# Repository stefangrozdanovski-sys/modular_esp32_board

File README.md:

# Modular ESP32 board (ESP32 Modular Base v2.0)

An open-hardware ESP32 carrier for Home Assistant / ESPHome. It has 8 JST XH 4-pin ports:

- **P1–P6**: general ports, each with a digital pin **A** and an input/analog pin **B**
- **UART**: 5 V serial port for meters and RS485 modules
- **I2C**: sensor bus with pull-ups fitted

There is also a switched output (**OUT**) for 12–24 V loads. Every general port has the same set of empty resistor footprints; you fit a few to match the job:

- **Generic jobs:** relays, buttons and dry contacts, temperature probes, 0–3.3 V analog signals, pulse and flow meters, energy meters, RS485 Modbus devices, I2C sensors and displays, 12–24 V loads (SSR, LED strip, fan, buzzer)
- **Popular parts:** 1–8 channel relay modules, DS18B20, NTC 10 k thermistors, YF-S201 / YF-B flow sensors, PZEM-004T v3, MAX485 modules, BME280, SHT3x / SHT4x, BH1750, ADS1115, SSD1306 OLED, capacitive soil moisture sensors

> **Status: v2.0 PCBs received from Seeed Studio (2026-11-05), not yet built or tested.**
> The picture below is rendered from the Gerbers, not a photo. Real photos and a test report will be added after bring-up.

## Features

- Ai-Thinker ESP-32S / ESP32-WROOM-32 module, USB (CH340C) with auto-reset, BOOT/RESET buttons, status LED
- 75 × 65 mm, 2 layers, hand-solderable (0805, 1206, SOT-23/223, SOIC-16, THT)
- Also suitable for machine assembly: standard SMD packages, assembly files for JLCPCB / PCBWay in `production/pcba/`
- 6 general ports P1–P6 (G, VP, A, B), UART port (5 V, RX divider for 5 V devices), I2C port (pull-ups fitted)
- OUT: low-side MOSFET switch with flyback diode, about 2 A / 24 V, PWM-capable
- Per port: VP jumper (3.3 V / 5 V), 0.5 A PTC, series resistors, empty footprints for pull-ups, pull-downs, divider and filter
- **Low voltage only.** No mains on the PCB. Mains devices (e.g. PZEM-004T, relay boards) stay in their own enclosure section behind a divider. Flash and probe the board with mains disconnected.

## Pin map

| Port | A (pin 3) | B (pin 4) | Notes |
|---|---|---|---|
| P1 | GPIO25 | GPIO36 | B input-only, ADC1. No pulse counting on GPIO36 |
| P2 | GPIO26 | GPIO39 | B input-only, ADC1. No pulse counting on GPIO39 |
| P3 | GPIO27 | GPIO34 | B input-only, ADC1 |
| P4 | GPIO13 | GPIO35 | B input-only, ADC1 |
| P5 | GPIO4 | GPIO32 | B bidirectional, ADC1 |
| P6 | GPIO18 | GPIO33 | B bidirectional, ADC1 |
| UART | TX GPIO17 | RX GPIO16 | VP = 5 V, RX through 10 k / 22 k divider |
| I2C | SDA GPIO21 | SCL GPIO22 | 4.7 k pull-ups fitted |
| OUT | GPIO23 → AO3400A | | XH 3P: G, V+, OUT |
| Fixed | GPIO0 BOOT, GPIO1/3 USB serial, GPIO2 status LED | | |

Connector pins: 1 GND, 2 VP, 3 A, 4 B (JST XH 2.54 mm, pin 1 = square pad).

## Port recipes

Fit the parts for the job, then use the matching ESPHome component.

| Job | Pin | VP | Fit | ESPHome |
|---|---|---|---|---|
| Relay module, low trigger | A | 3V3 | defaults | `switch: gpio`, `inverted: true` |
| Relay module, high trigger | A | 3V3 | + RAD 10 k | `switch: gpio` |
| DS18B20 | A | 3V3 | + RAU 4.7 k | `one_wire` + `dallas_temp` |
| Button / dry contact | A | – | internal pull-up (or RAU 10 k) | `binary_sensor: gpio` |
| NTC 10 k B3950 | B | – | + RBU 10 k 1 %, CB 100 nF | `adc` → `resistance` → `ntc` |
| 0–3.3 V analog | B | as needed | + CB 100 nF | `adc` |
| 5 V pulse (flow sensor) | B on P3–P6 | 5V | RB → 10 k, + RBD 22 k, CB 1 nF | `pulse_counter` |
| Open-collector pulse | A | 5V | + RAU 10 k | `pulse_counter` |
| PZEM-004T | UART | 5V | defaults | `uart` + `modbus` + `pzemac` |
| RS485 Modbus | UART + P5/P6 B (DE/RE) | 5V | remove R706 for a 3.3 V module | `modbus` with `flow_control_pin` |
| I2C sensors | I2C | 3V3 | defaults | `i2c` + sensor |
| SSR / LED strip / fan / buzzer | OUT | load supply | defaults | `output: ledc` or `gpio` |

Part names per port (n = port number, 7 = UART, 8 = I2C): Rn01 RA series, Rn02 RAU, Rn03 RAD, Rn04 RB series, Rn05 RBU, Rn06 RBD, Cn01 CB. Full details: the "Port options" sheet in [the BOM workbook](hardware/bom/esp32-modular-v2.0-BOM.xlsx) and page 13+ of the assembly guide.

## Build one

**Bare PCB:** upload [`hardware/fabrication/esp32-modular_gerbers.zip`](hardware/fabrication/esp32-modular_gerbers.zip) to JLCPCB, PCBWay or Seeed Fusion: 2 layers, 75 × 65 mm, 1.6 mm, 1 oz, HASL lead-free (ENIG is nicer for the module's castellated pads). All rules are within the standard tier.

**Hand assembly:**
- [Assembly guide (A4 PDF, 17 pages)](hardware/docs/assembly_guide.pdf): one page per soldering step, inspection and test pages
- [Interactive BOM](hardware/docs/ibom_assembly.html): download it and open it in a browser, then click a part to see where it goes
- [BOM workbook](hardware/bom/esp32-modular-v2.0-BOM.xlsx) and [BOM app](hardware/bom/bom-app.html) (offline shopping list: stock, shops, number of boards)
- [Schematic (PDF)](hardware/docs/schematic.pdf)

**Assembled by the fab (PCBA):** JLCPCB and PCBWay BOM and position files are in [`production/pcba/`](production/pcba/README.md). They cover the 54 SMD parts; you hand-solder the 14 THT parts (XH sockets, buttons, electrolytics) or pay JLCPCB for THT assembly. The fab build uses an ESP32-WROOM-32E-N4 instead of the Ai-Thinker ESP-32S. All LCSC numbers were checked on JLCPCB (2026-11-05). **Before ordering:** confirm part rotations in JLCPCB's placement preview (see that README).

## Firmware

ESPHome packages in [`firmware/`](firmware/README.md): one package per port job (relay, dry contact, DS18B20, NTC, analog, pulse flow, PZEM-004T, RS485 Modbus, I2C + BME280, OUT PWM / switch), a common `base.yaml` with the board pins as substitutions, and three examples (`test-board`, `energy-relay`, `greenhouse`).

Pick the job, fit the parts from the recipe above, then include the package with the port pin:

```yaml
packages:
  base: !include ../base.yaml
  pump_p1: !include
    file: ../packages/relay.yaml
    vars: {id: pump_p1, name: Pump, pin: "${p1_a}"}
```

Every example passes `esphome config` on ESPHome 2026.10.2 (ESP-IDF framework). Not yet run on a built board. New board: flash `firmware/examples/test-board.yaml` first (assembly guide page 13).

## Setup notes

- [ ] **PCBA:** confirm every part's rotation and pin 1 in JLCPCB's placement preview before any assembled order (see [`production/pcba/README.md`](production/pcba/README.md)).
- [ ] **Flow sensors:** set `pulses_per_litre` for each flow sensor model used. One board set can use different models, so set it per sensor (typical values in [`firmware/README.md`](firmware/README.md#flow-sensor-factors)).
- [ ] **Device sets:** the examples are starting points. Write one device config per board set (which devices on which ports), named after the board (e.g. `b1-boiler.yaml`).

## Repository

| Folder | Contents |
|---|---|
| `firmware/` | ESPHome packages and example configs. See [firmware/README.md](firmware/README.md) |
| `hardware/` | KiCad 7 project, custom footprint library, generator scripts (`tools/`), BOM (`bom/`), docs and Gerbers. See [hardware/README.md](hardware/README.md) |
| `production/pcba/` | JLCPCB / PCBWay BOM and position files, generated by `hardware/tools/pcba.py` |
| `LICENSES/` | Licence texts |

The KiCad files are generated by Python scripts (`hardware/tools/`): `parts.py` and `design.py` are the source of truth. Rebuild steps and the toolchain (KiCad 7, Freerouting 1.9.0, InteractiveHtmlBom, …) are in [hardware/README.md](hardware/README.md). KiCad 8/9 open the files and upgrade them on save.

## Known caveats

- Hardware not yet built or tested. Faults found during bring-up will be logged in [CHANGELOG.md](CHANGELOG.md) and the issues.
- Electrical check done with a netlist pin-type script (`erc_lite.py`), not a full KiCad GUI ERC. Expected finding: CH340C V3 and AMS1117 output both on +3V3 (CH340C 3.3 V mode).
- Six reference designators are hidden on the silkscreen for lack of room. The iBOM and assembly guide show all of them.
- Iron temperatures and test values in the assembly guide are general guidance, not measurements from a built board.

## Licence

| What | Licence |
|---|---|
| Hardware design (KiCad files, footprints, Gerbers) | [CERN-OHL-S-2.0](LICENSES/CERN-OHL-S-2.0.txt) |
| Scripts and firmware | [MIT](LICENSES/MIT.txt) |
| Documentation and images | [CC BY-SA 4.0](LICENSES/CC-BY-SA-4.0.txt) |

© 2026 stefangrozdanovski-sys. Freerouting (used to route the board, downloaded by `hardware/tools/get_freerouting.sh`) is GPL-3.0 and not included.

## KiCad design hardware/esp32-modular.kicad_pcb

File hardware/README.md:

# ESP32 Modular Base v2.0: hardware

75 × 65 mm, 2 layers, 1.6 mm FR-4. Hand-solderable (0805, 1206, SOT-23/223, SOIC-16, THT).
Low-voltage board only: USB 5 V in, no mains on the PCB.

## Connectors

| Edge | Connector | Pins (pin 1 = square pad) |
|---|---|---|
| Top-right | J1 USB in (XH 4P) | 5V, D−, D+, G (from the bare USB-C breakout, A-to-C cable) |
| Bottom | P1–P4 (J101–J401, XH 4P) | G, VP, A, B |
| Left | P5, P6 (J501, J601, XH 4P) | G, VP, A, B |
| Right | UART (J701), I2C (J801), XH 4P | G, VP, TX, RX / G, VP, SDA, SCL |
| Right | OUT (J901, XH 3P) | G, V+, OUT |
| Under module | EXP (J902, 1×5 2.54 mm, not fitted) | 3V3, IO19, IO14, IO5, G |
| Top-left | RESET, BOOT buttons | |

## Pin map

| Port | A (pin 3) | B (pin 4) | Notes |
|---|---|---|---|
| P1 | IO25 | IO36 | B input-only, ADC1. No pulse counting on IO36 |
| P2 | IO26 | IO39 | B input-only, ADC1. No pulse counting on IO39 |
| P3 | IO27 | IO34 | B input-only, ADC1 |
| P4 | IO13 | IO35 | B input-only, ADC1 |
| P5 | IO4 | IO32 | B bidirectional, ADC1 |
| P6 | IO18 | IO33 | B bidirectional, ADC1 |
| UART | TX IO17 | RX IO16 | RX through 10k/22k divider (5 V devices) |
| I2C | SDA IO21 | SCL IO22 | 4.7 k pull-ups fitted |
| OUT | IO23 → AO3400A | | low-side, SS34 flyback to V+, about 2 A / 24 V |
| Fixed | IO0 BOOT, IO1/IO3 CH340C, IO2 status LED | | |

The port map is also printed on the back of the board.

## Port options (same in every port, n = port number, 7 = UART, 8 = I2C)

| Ref | Position | Default |
|---|---|---|
| JPn01 | VP jumper: pad next to the connector = 3V3, far pad = 5V | 3V3 (UART: 5V), bridged by a trace |
| Fn01 | 0.5 A PTC on VP | fitted |
| Rn01 | A series | 330 R |
| Rn02 / Rn03 | A pull-up to 3V3 / pull-down to GND | empty |
| Rn04 | B series | 1 k |
| Rn05 | B pull-up to 3V3 (connector side) | empty |
| Rn06 / Cn01 | B to GND (GPIO side): divider bottom / filter | empty |

To change a VP jumper: cut the thin trace between the bridged pads, then bridge the other side with solder.
Recipes for each job (relay, NTC, DS18B20, flow sensor, PZEM, I2C) are on the "Port options" sheet of `bom/esp32-modular-v2.0-BOM.xlsx`.

## Buying the parts

Open `bom/bom-app.html` in your browser (works offline). Enter what you have in stock, set the number of boards, choose the shop per part, then open the Shopping list tab and print it on A4. Everything is saved in that browser; use Export backup to keep a copy. Rebuild it with `python3 bom/build_bom_app.py bom/bom-app.html` after the BOM changes.

## Ordering

Upload `fabrication/esp32-modular_gerbers.zip` to PCBWay or JLCPCB: 2 layers, 75 × 65 mm, 1.6 mm, 1 oz, HASL lead-free (ENIG is nicer for the castellated module).
Rules used: 0.2 mm clearance, 0.3 mm signal / 0.4 mm power tracks, 0.7/0.35 mm vias (tented), 0.5 mm copper to edge. All within the standard tier.

## Assembly order

Print `docs/assembly_guide.pdf` (17 A4 pages): one page per soldering step with the parts highlighted on a board drawing, tick boxes for boards B1–B5, inspection, test pages with measurement columns, port options, jumper how-to, a board record and a parts index.

Open `docs/ibom_assembly.html` in a browser: click a BOM line and its parts light up on the board (pin 1 marked). Tick Sourced / Placed as you go; the ticks are remembered in that browser. Empty option footprints are not listed.

1. Fine pitch first, board flat: U3 CH340C, U4 USBLC6, Q1, Q2, Q901, U2 AMS1117.
2. 0805 / 1206 parts: the core first, then each port's fitted parts (Rn01 330 R, Rn04 1 k, Fn01 PTC, plus R706 22 k, R704 10 k, R802/R805 4.7 k).
   Leave the option footprints empty until you know what goes on that port.
3. D1 SMAJ5.0A and D901 SS34 (band toward +5V / V+), F1, LEDs (cathode toward GND).
4. U1 ESP-32S: tin pad 1, align, tack pads 1 and 38, check, then drag-solder. Optionally solder the centre GND pad through the hole from the back.
5. THT: SW1/SW2, C1/C4 (mind the +), XH sockets.

## Bring-up

1. Unpowered: +5V–GND and +3V3–GND are not shorted.
2. Power from USB: +5V ≈ 4.9–5.1 V, +3V3 = 3.25–3.35 V, red LED on.
3. Plug into a PC: the CH340 appears as a serial port. Flash ESPHome; auto-reset handles boot mode (or hold BOOT, tap RESET).

## Verification done

- Netlist vs `tools/design.py`: 73 nets, 119 parts, 0 differences. Pin-type electrical check: only the documented CH340C 3.3 V mode finding.
- KiCad 7 DRC: 0 violations, 0 unconnected items, 0 footprint errors.
- PCB vs schematic: all 325 pads carry the schematic's net.
- Gerbers re-read with gerbv; `docs/board_top.png` / `board_bottom.png` are rendered from the Gerbers.

## Rebuilding (tools/)

`parts.py` (values, footprints, fit) and `design.py` (nets) are the source of truth; `layout.py` holds the board geometry and placement.

```
python3 tools/gen_sch.py esp32-modular.kicad_sch
kicad-cli sch export netlist -o net.net esp32-modular.kicad_sch
python3 tools/check_net.py net.net && python3 tools/erc_lite.py net.net
python3 tools/build_pcb.py net.net placed.kicad_pcb
python3 tools/silk_fix.py placed.kicad_pcb silk.kicad_pcb --keepout
bash tools/get_freerouting.sh                                    # once: downloads Freerouting 1.9.0 (GPL-3.0)
python3 tools/route.py silk.kicad_pcb routed.kicad_pcb 60        # Freerouting 1.9.0, optimizer off
python3 tools/finish.py routed.kicad_pcb fin.kicad_pcb drc.txt --stitch
python3 tools/polish.py fin.kicad_pcb esp32-modular.kicad_pcb net.net
python3 tools/verify_pcb.py esp32-modular.kicad_pcb net.net drc.txt
bash tools/export.sh .
python3 tools/board_geom.py esp32-modular.kicad_pcb docs/assembly/geom.json
python3 tools/assembly_book.py docs/assembly/geom.json docs/assembly/assembly_guide.html
python3 tools/print_pdf.py docs/assembly/assembly_guide.html docs/assembly_guide.pdf     # A4 assembly guide
bash tools/make_ibom.sh . net.net                                # docs/ibom_assembly.html
python3 tools/gerber_render.py fabrication/gerbers docs/board_top.png docs/board_bottom.png
python3 bom/build_bom.py bom/esp32-modular-v2.0-BOM.xlsx
```

In a bare Python session set `KICAD7_FOOTPRINT_DIR=/usr/share/kicad/footprints`. Remove the `silk: no vias` rule areas after routing (done before saving the project board).

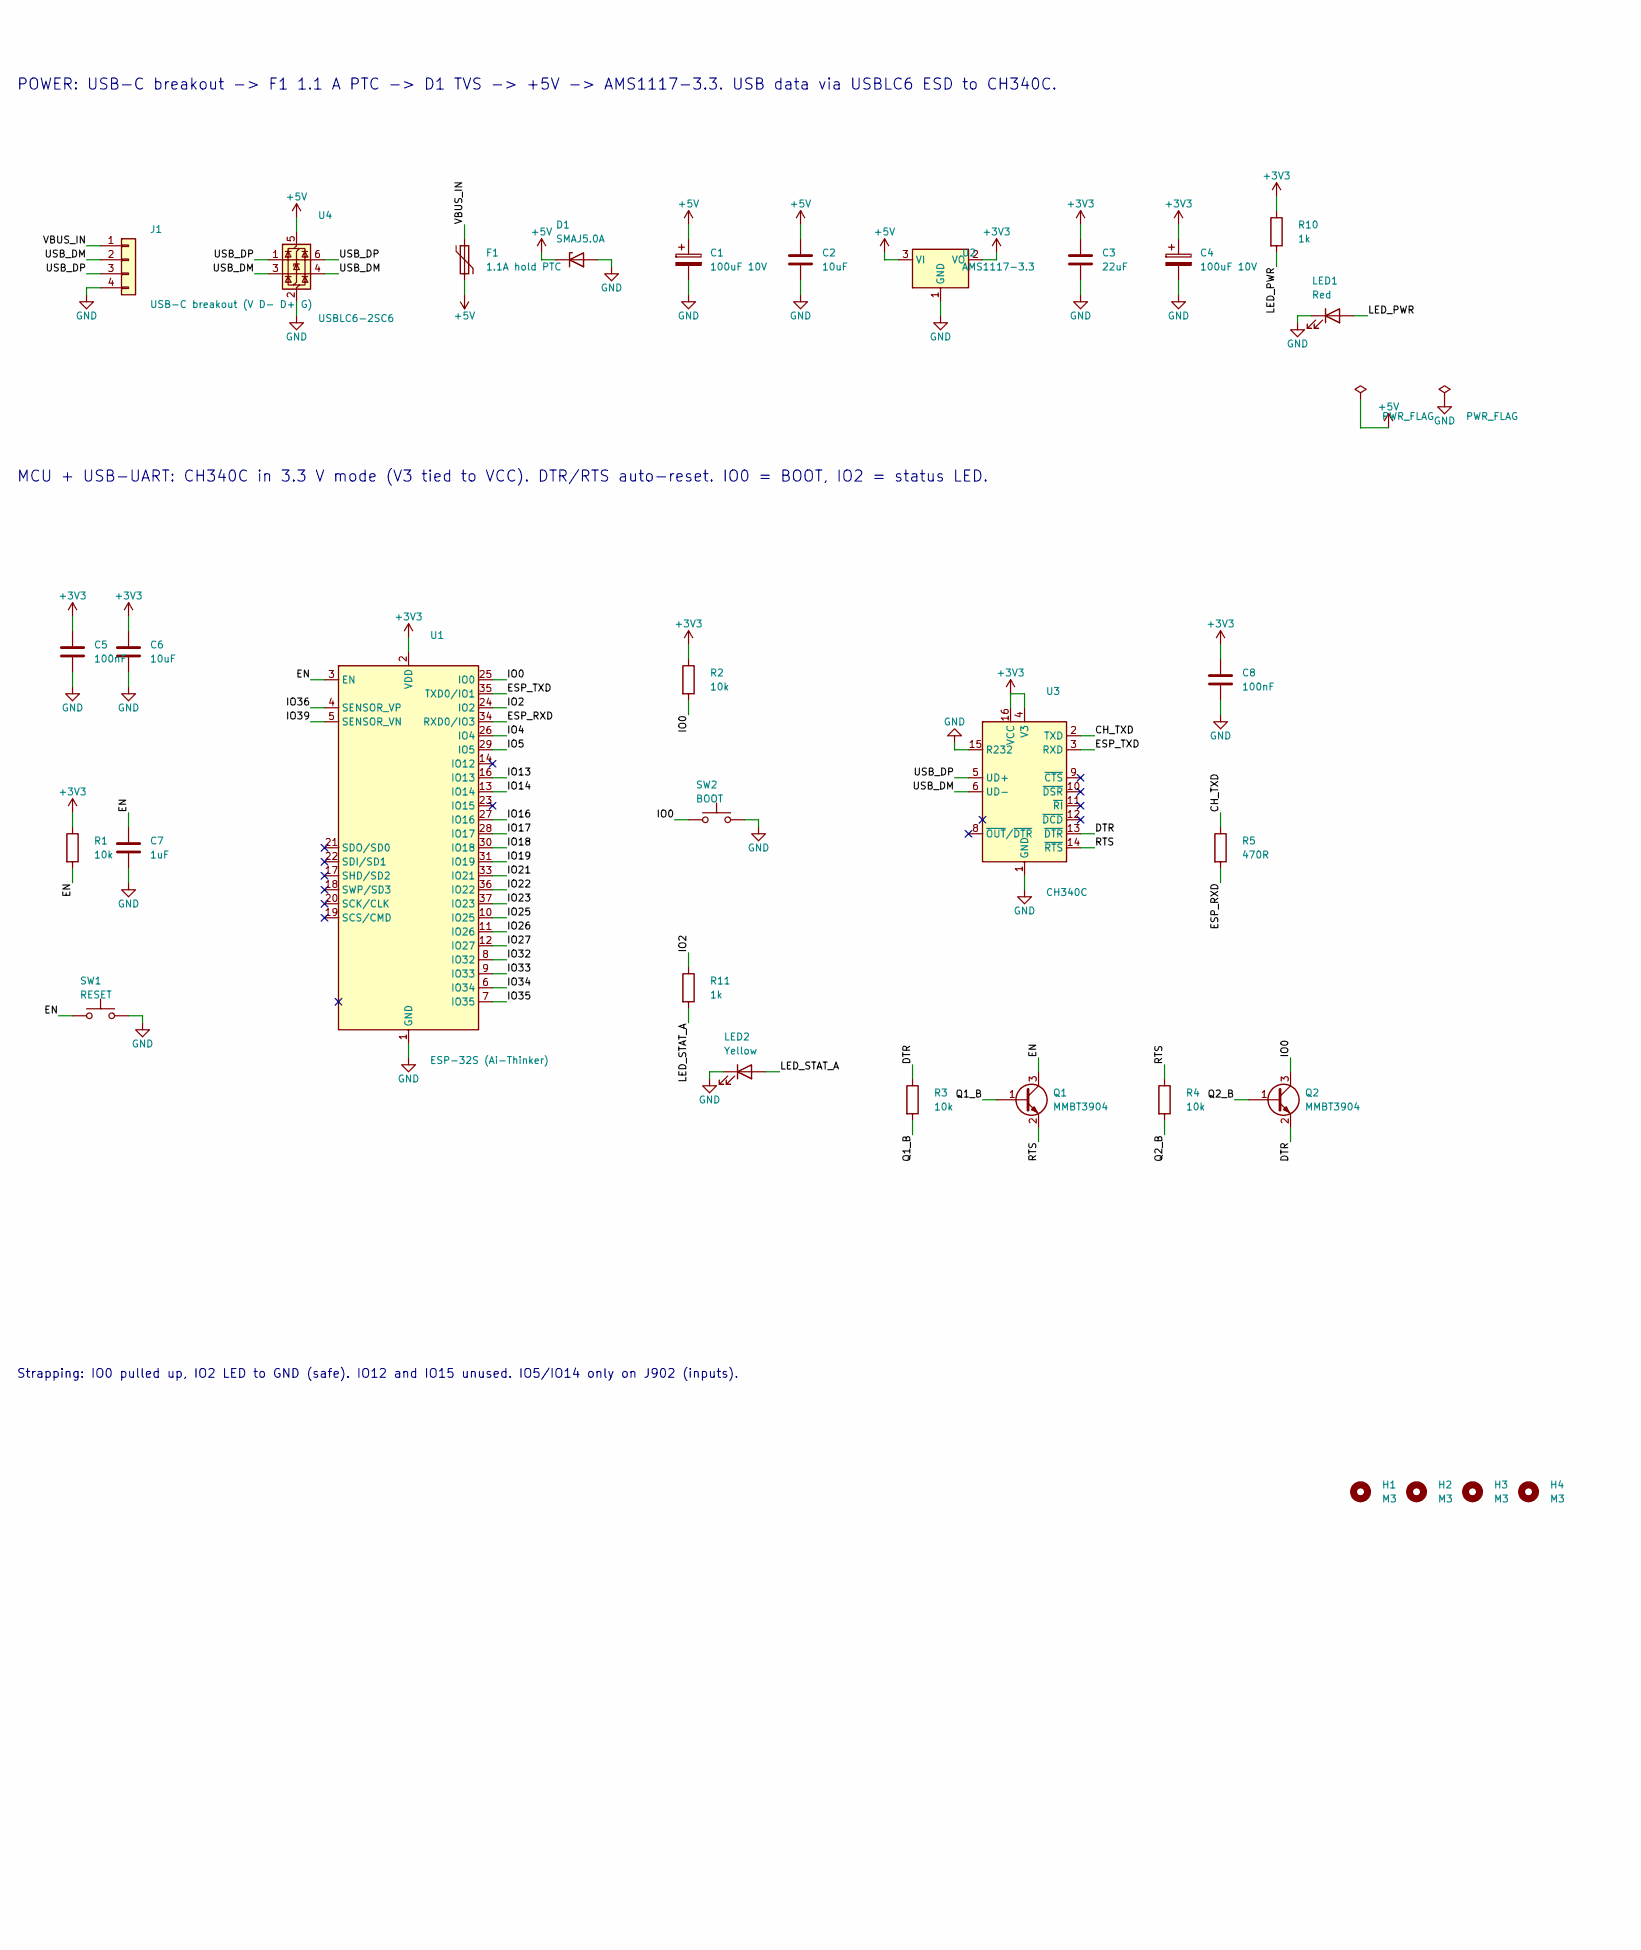
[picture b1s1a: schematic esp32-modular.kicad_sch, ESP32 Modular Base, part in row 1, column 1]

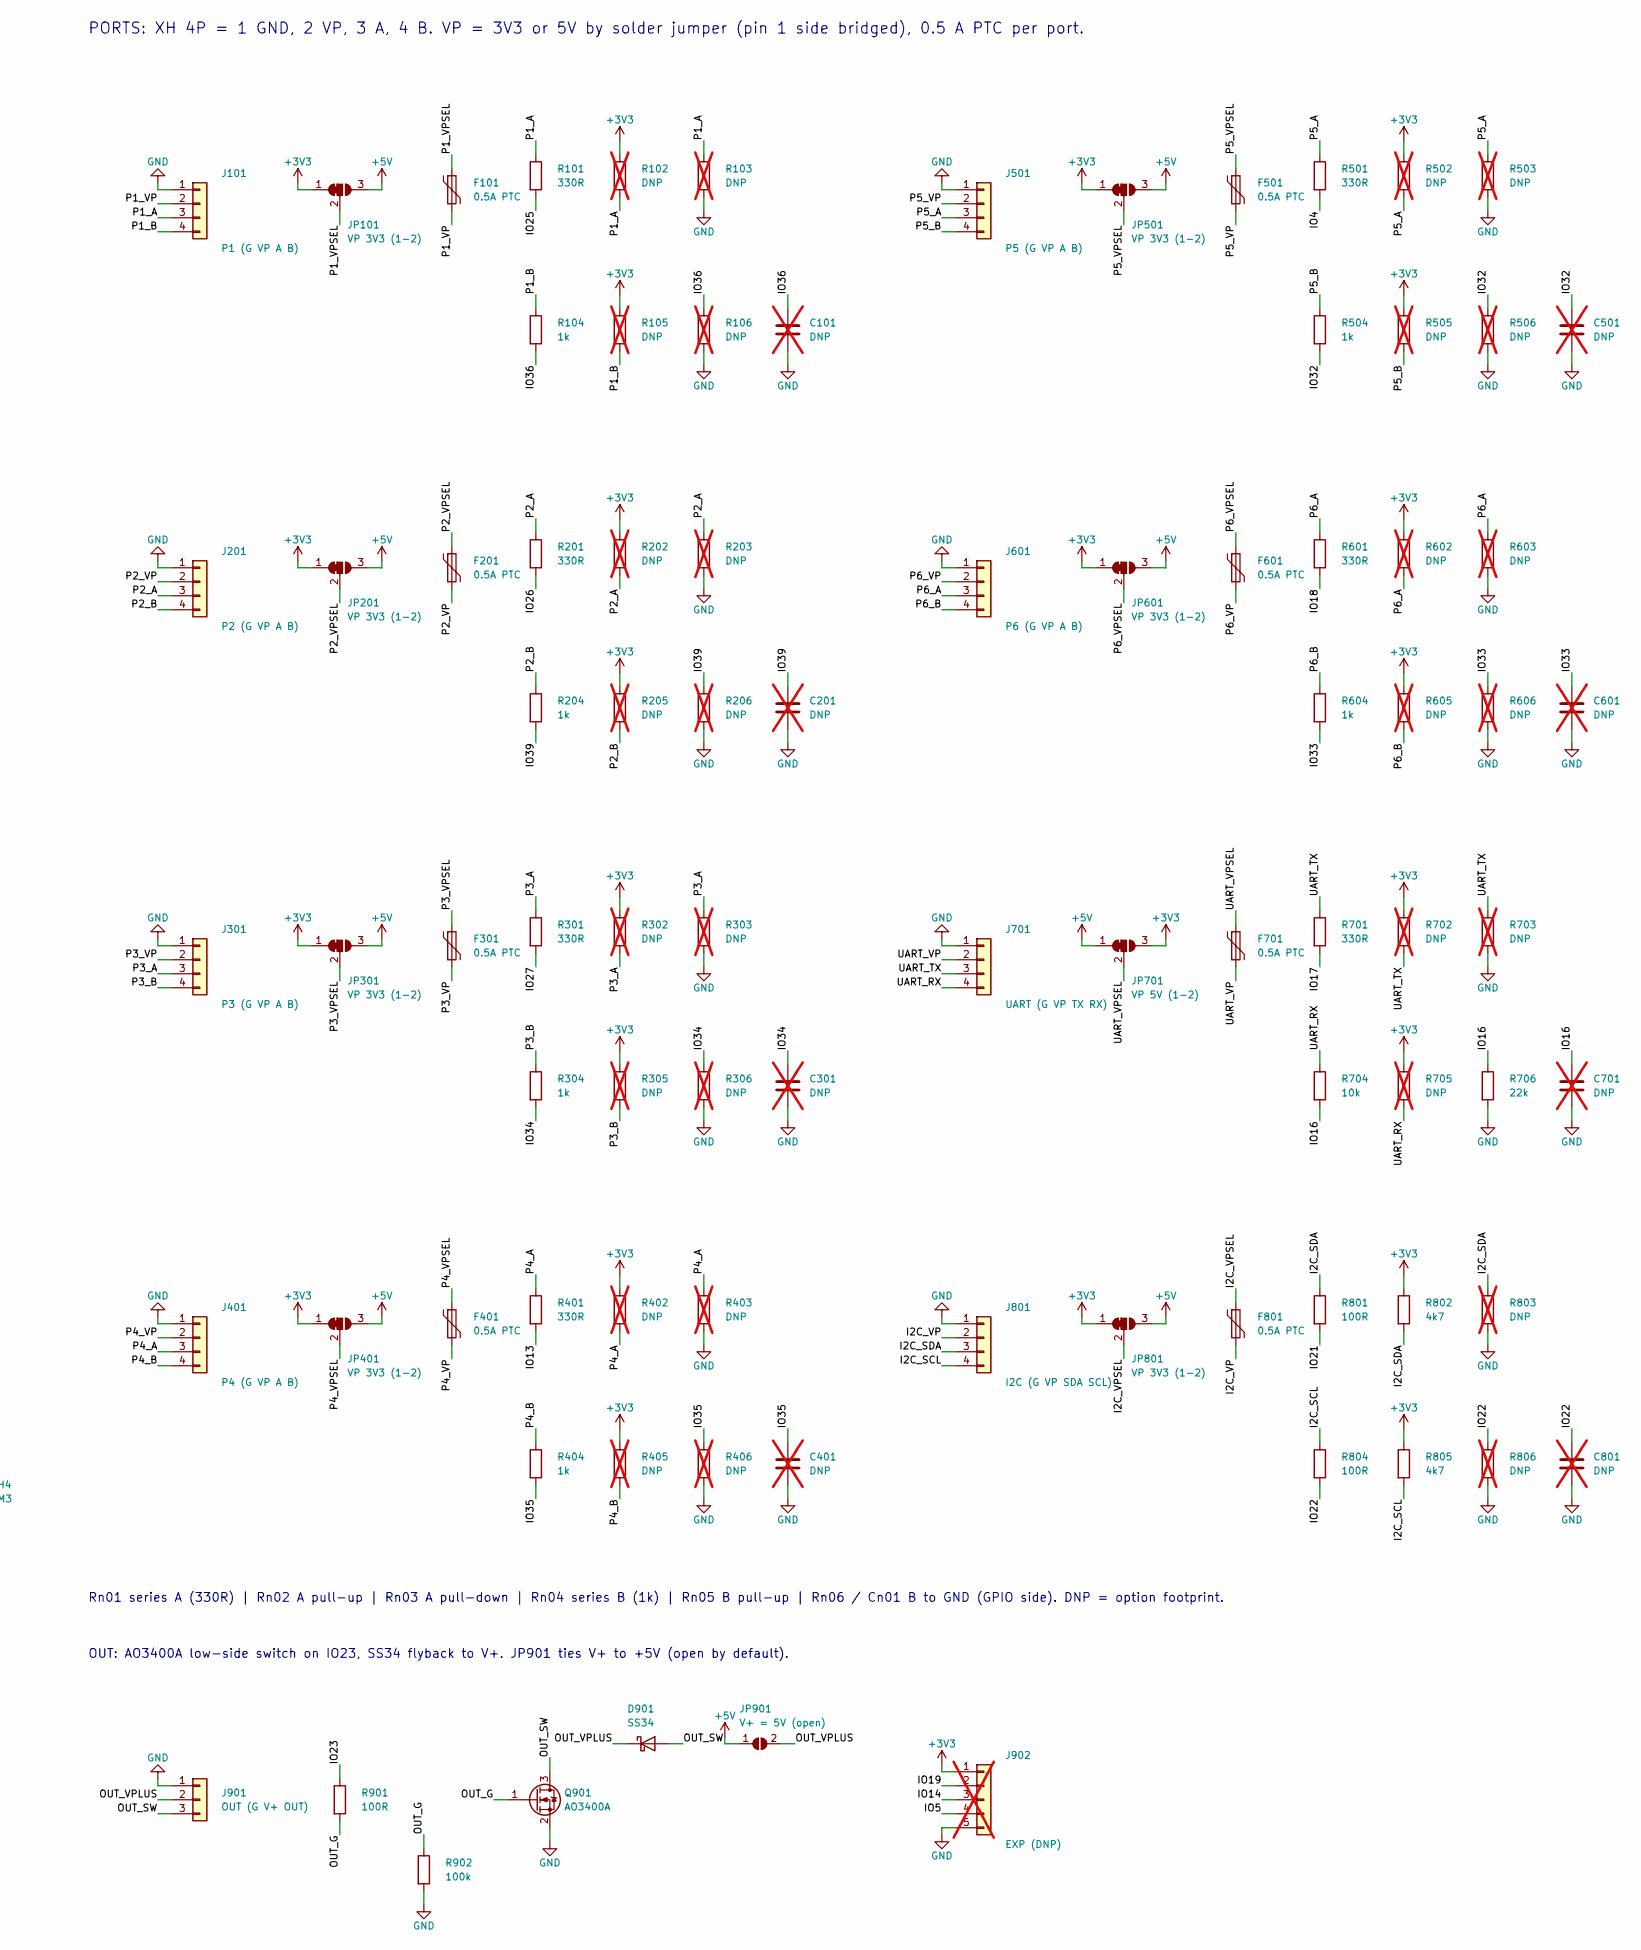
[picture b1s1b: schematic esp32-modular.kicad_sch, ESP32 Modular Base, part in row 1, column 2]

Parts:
C1, C4: 100uF 10V; CP_Radial_D6.3mm_P2.50mm
C2, C6: 10uF; C_0805_2012Metric_Pad1.18x1.45mm_HandSolder
C3: 22uF; C_0805_2012Metric_Pad1.18x1.45mm_HandSolder
C5, C8: 100nF; C_0805_2012Metric_Pad1.18x1.45mm_HandSolder
C7: 1uF; C_0805_2012Metric_Pad1.18x1.45mm_HandSolder
C101, C201, C301, C401, C501, C601, C701, C801: DNP; C_0805_2012Metric_Pad1.18x1.45mm_HandSolder; not fitted
D1: SMAJ5.0A; D_SMA_Handsoldering
D901: SS34; D_SMA_Handsoldering
F1: 1.1A hold PTC; Fuse_1812_4532Metric_Pad1.30x3.40mm_HandSolder
F101, F201, F301, F401, F501, F601, F701, F801: 0.5A PTC; Fuse_1206_3216Metric_Pad1.42x1.75mm_HandSolder
H1, H2, H3, H4: M3; MountingHole_3.2mm_M3
J1: USB-C breakout (V D- D+ G); JST_XH_B4B-XH-A_1x04_P2.50mm_Vertical
J101: P1 (G VP A B); JST_XH_B4B-XH-A_1x04_P2.50mm_Vertical
J201: P2 (G VP A B); JST_XH_B4B-XH-A_1x04_P2.50mm_Vertical
J301: P3 (G VP A B); JST_XH_B4B-XH-A_1x04_P2.50mm_Vertical
J401: P4 (G VP A B); JST_XH_B4B-XH-A_1x04_P2.50mm_Vertical
J501: P5 (G VP A B); JST_XH_B4B-XH-A_1x04_P2.50mm_Vertical
J601: P6 (G VP A B); JST_XH_B4B-XH-A_1x04_P2.50mm_Vertical
J701: UART (G VP TX RX); JST_XH_B4B-XH-A_1x04_P2.50mm_Vertical
J801: I2C (G VP SDA SCL); JST_XH_B4B-XH-A_1x04_P2.50mm_Vertical
J901: OUT (G V+ OUT); JST_XH_B3B-XH-A_1x03_P2.50mm_Vertical
J902: EXP (DNP); PinHeader_1x05_P2.54mm_Vertical; not fitted
JP101, JP201, JP301, JP401, JP501, JP601, JP801: VP 3V3 (1-2); SolderJumper-3_P1.3mm_Bridged12_RoundedPad1.0x1.5mm
JP701: VP 5V (1-2); SolderJumper-3_P1.3mm_Bridged12_RoundedPad1.0x1.5mm
JP901: V+ = 5V (open); SolderJumper-2_P1.3mm_Open_RoundedPad1.0x1.5mm
LED1: Red; LED_0805_2012Metric_Pad1.15x1.40mm_HandSolder
LED2: Yellow; LED_0805_2012Metric_Pad1.15x1.40mm_HandSolder
Q1, Q2: MMBT3904; SOT-23
Q901: AO3400A; SOT-23
R1, R2, R3, R4, R704: 10k; R_0805_2012Metric_Pad1.20x1.40mm_HandSolder
R5: 470R; R_0805_2012Metric_Pad1.20x1.40mm_HandSolder
R10, R11, R104, R204, R304, R404, R504, R604: 1k; R_0805_2012Metric_Pad1.20x1.40mm_HandSolder
R101, R201, R301, R401, R501, R601, R701: 330R; R_0805_2012Metric_Pad1.20x1.40mm_HandSolder
R102, R103, R105, R106, R202, R203, R205, R206, R302, R303, R305, R306, R402, R403, R405, R406, R502, R503, R505, R506, R602, R603, R605, R606, R702, R703, R705, R803, R806: DNP; R_0805_2012Metric_Pad1.20x1.40mm_HandSolder; not fitted
R706: 22k; R_0805_2012Metric_Pad1.20x1.40mm_HandSolder
R801, R804, R901: 100R; R_0805_2012Metric_Pad1.20x1.40mm_HandSolder
R802, R805: 4k7; R_0805_2012Metric_Pad1.20x1.40mm_HandSolder
R902: 100k; R_0805_2012Metric_Pad1.20x1.40mm_HandSolder
SW1: RESET; SW_PUSH_6mm
SW2: BOOT; SW_PUSH_6mm
U1: ESP-32S (Ai-Thinker); ESP32-WROOM-32_HandSolder
U2: AMS1117-3.3; SOT-223-3_TabPin2
U3: CH340C; SOIC-16_3.9x9.9mm_P1.27mm
U4: USBLC6-2SC6; SOT-23-6

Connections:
+3V3: C3.1, C4.1, C5.1, C6.1, C8.1, J902.1, JP101.1 (A), JP201.1 (A), JP301.1 (A), JP401.1 (A), JP501.1 (A), JP601.1 (A), JP701.3 (B), JP801.1 (A), R1.1, R2.1, R10.1, R102.1, R105.1, R202.1, R205.1, R302.1, R305.1, R402.1, R405.1, R502.1, R505.1, R602.1, R605.1, R702.1, R705.1, R802.1, R805.1, U1.2 (VDD), U2.2 (VO), U3.4 (V3), U3.16 (VCC)
+5V: C1.1, C2.1, D1.1 (K), F1.2, JP101.3 (B), JP201.3 (B), JP301.3 (B), JP401.3 (B), JP501.3 (B), JP601.3 (B), JP701.1 (A), JP801.3 (B), JP901.1 (A), U2.3 (VI), U4.5 (VBUS)
/CH_TXD: R5.1, U3.2 (TXD)
/DTR: Q2.2 (E), R3.1, U3.13 (~DTR)
/EN: C7.1, Q1.3 (C), R1.2, SW1.1, U1.3 (EN)
/ESP_RXD: R5.2, U1.34 (RXD0/IO3)
/ESP_TXD: U1.35 (TXD0/IO1), U3.3 (RXD)
/I2C_SCL: J801.4, R804.1, R805.2
/I2C_SDA: J801.3, R801.1, R802.2, R803.1
/I2C_VP: F801.2, J801.2
/I2C_VPSEL: F801.1, JP801.2 (C)
/IO0: Q2.3 (C), R2.2, SW2.1, U1.25 (IO0)
/IO2: R11.1, U1.24 (IO2)
/IO4: R501.2, U1.26 (IO4)
/IO5: J902.4, U1.29 (IO5)
/IO13: R401.2, U1.16 (IO13)
/IO14: J902.3, U1.13 (IO14)
/IO16: C701.1, R704.2, R706.1, U1.27 (IO16)
/IO17: R701.2, U1.28 (IO17)
/IO18: R601.2, U1.30 (IO18)
/IO19: J902.2, U1.31 (IO19)
/IO21: R801.2, U1.33 (IO21)
/IO22: C801.1, R804.2, R806.1, U1.36 (IO22)
/IO23: R901.1, U1.37 (IO23)
/IO25: R101.2, U1.10 (IO25)
/IO26: R201.2, U1.11 (IO26)
/IO27: R301.2, U1.12 (IO27)
/IO32: C501.1, R504.2, R506.1, U1.8 (IO32)
/IO33: C601.1, R604.2, R606.1, U1.9 (IO33)
/IO34: C301.1, R304.2, R306.1, U1.6 (IO34)
/IO35: C401.1, R404.2, R406.1, U1.7 (IO35)
/IO36: C101.1, R104.2, R106.1, U1.4 (SENSOR_VP)
/IO39: C201.1, R204.2, R206.1, U1.5 (SENSOR_VN)
/LED_PWR: LED1.2 (A), R10.2
/LED_STAT_A: LED2.2 (A), R11.2
/OUT_G: Q901.1 (G), R901.2, R902.1
/OUT_SW: D901.2 (A), J901.3, Q901.3 (D)
/OUT_VPLUS: D901.1 (K), J901.2, JP901.2 (B)
/P1_A: J101.3, R101.1, R102.2, R103.1
/P1_B: J101.4, R104.1, R105.2
/P1_VP: F101.2, J101.2
/P1_VPSEL: F101.1, JP101.2 (C)
/P2_A: J201.3, R201.1, R202.2, R203.1
/P2_B: J201.4, R204.1, R205.2
/P2_VP: F201.2, J201.2
/P2_VPSEL: F201.1, JP201.2 (C)
/P3_A: J301.3, R301.1, R302.2, R303.1
/P3_B: J301.4, R304.1, R305.2
/P3_VP: F301.2, J301.2
/P3_VPSEL: F301.1, JP301.2 (C)
/P4_A: J401.3, R401.1, R402.2, R403.1
/P4_B: J401.4, R404.1, R405.2
/P4_VP: F401.2, J401.2
/P4_VPSEL: F401.1, JP401.2 (C)
/P5_A: J501.3, R501.1, R502.2, R503.1
/P5_B: J501.4, R504.1, R505.2
/P5_VP: F501.2, J501.2
/P5_VPSEL: F501.1, JP501.2 (C)
/P6_A: J601.3, R601.1, R602.2, R603.1
/P6_B: J601.4, R604.1, R605.2
/P6_VP: F601.2, J601.2
/P6_VPSEL: F601.1, JP601.2 (C)
/Q1_B: Q1.1 (B), R3.2
/Q2_B: Q2.1 (B), R4.2
/RTS: Q1.2 (E), R4.1, U3.14 (~RTS)
/UART_RX: J701.4, R704.1, R705.2
/UART_TX: J701.3, R701.1, R702.2, R703.1
/UART_VP: F701.2, J701.2
/UART_VPSEL: F701.1, JP701.2 (C)
/USB_DM: J1.2, U3.6 (UD-), U4.3 (I/O2), U4.4 (I/O2)
/USB_DP: J1.3, U3.5 (UD+), U4.1 (I/O1), U4.6 (I/O1)
/VBUS_IN: F1.1, J1.1
GND: C1.2, C2.2, C3.2, C4.2, C5.2, C6.2, C7.2, C8.2, C101.2, C201.2, C301.2, C401.2, C501.2, C601.2, C701.2, C801.2, D1.2 (A), J1.4, J101.1, J201.1, J301.1, J401.1, J501.1, J601.1, J701.1, J801.1, J901.1, J902.5, LED1.1 (K), LED2.1 (K), Q901.2 (S), R103.2, R106.2, R203.2, R206.2, R303.2, R306.2, R403.2, R406.2, R503.2, R506.2, R603.2, R606.2, R703.2, R706.2, R803.2, R806.2, R902.2, SW1.2, SW2.2, U1.1 (GND), U1.15 (GND), U1.38 (GND), U1.39 (GND), U2.1 (GND), U3.1 (GND), U3.15 (R232), U4.2 (GND)

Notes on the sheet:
POWER: USB-C breakout -> F1 1.1 A PTC -> D1 TVS -> +5V -> AMS1117-3.3. USB data via USBLC6 ESD to CH340C.
MCU + USB-UART: CH340C in 3.3 V mode (V3 tied to VCC). DTR/RTS auto-reset. IO0 = BOOT, IO2 = status LED.
Strapping: IO0 pulled up, IO2 LED to GND (safe). IO12 and IO15 unused. IO5/IO14 only on J902 (inputs).
PORTS: XH 4P = 1 GND, 2 VP, 3 A, 4 B. VP = 3V3 or 5V by solder jumper (pin 1 side bridged), 0.5 A PTC per port.
Rn01 series A (330R) | Rn02 A pull-up | Rn03 A pull-down | Rn04 series B (1k) | Rn05 B pull-up | Rn06 / Cn01 B to GND (GPIO side). DNP = option footprint.
OUT: AO3400A low-side switch on IO23, SS34 flyback to V+. JP901 ties V+ to +5V (open by default).

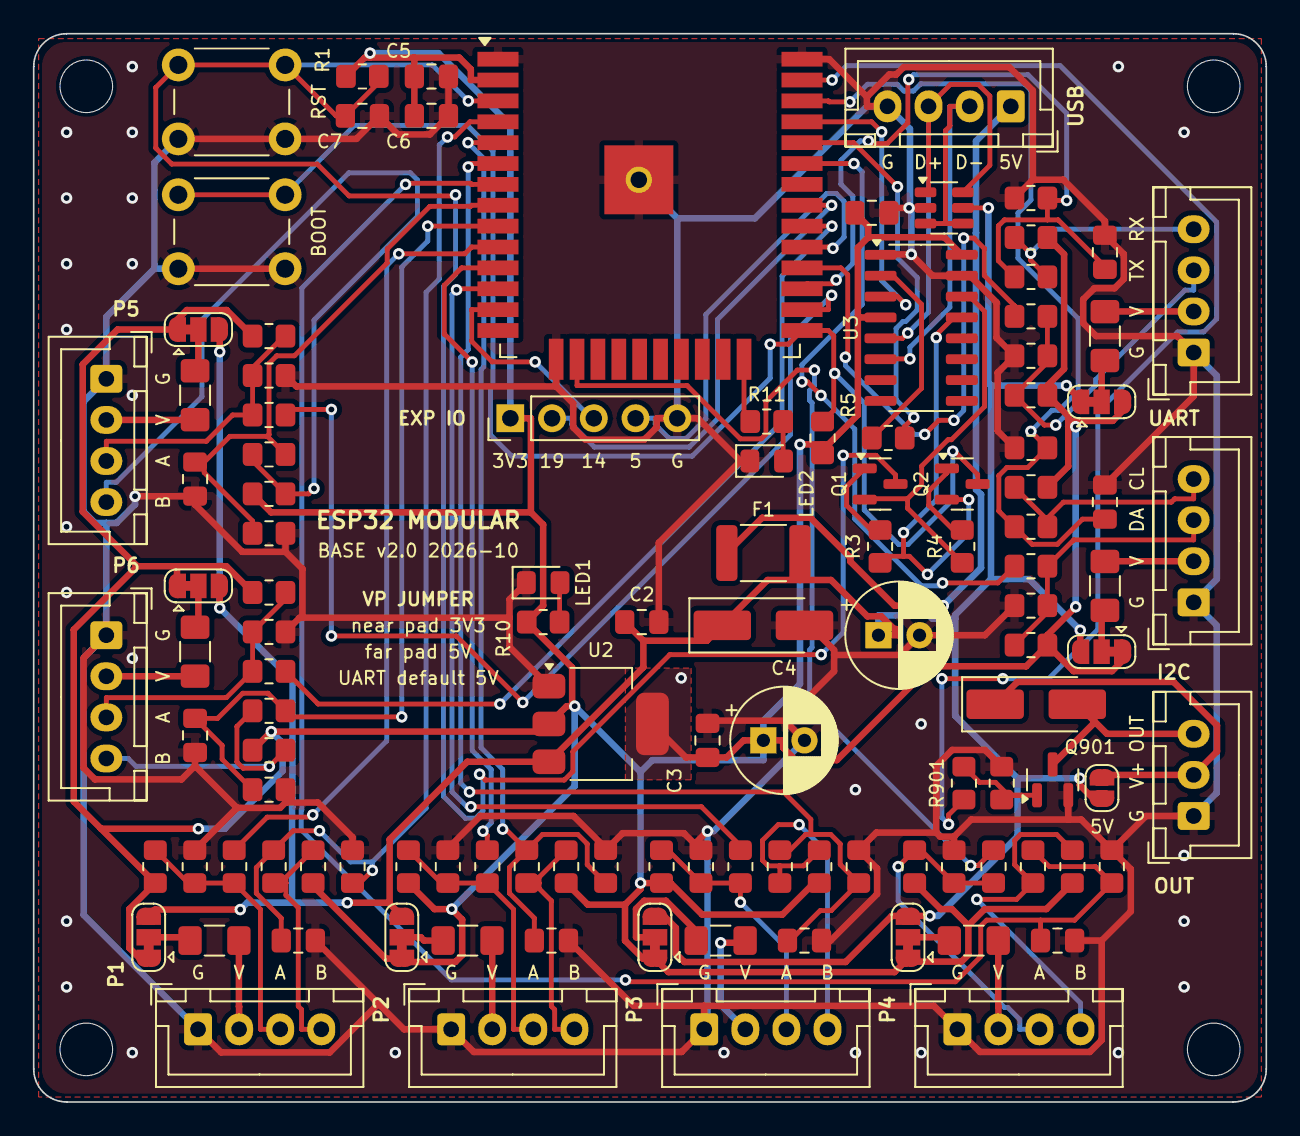
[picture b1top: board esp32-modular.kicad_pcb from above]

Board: 2 copper layers, 75.0 x 65.0 mm, 119 parts (0 on the bottom side), 73 nets.

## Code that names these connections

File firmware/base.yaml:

# SPDX-FileCopyrightText: 2026 stefangrozdanovski-sys
# SPDX-License-Identifier: MIT
#
# ESP32 Modular Base v2.0 - common board config.
# Include it first, from every device config:
#
#   substitutions:
#     device_name: my-device          # hostname: lowercase, digits, "-"
#     friendly_name: My device
#   packages:
#     base: !include ../base.yaml
#
# Needs firmware/secrets.yaml, next to this file (copy secrets.example.yaml).
# Framework: ESP-IDF (ESPHome default). No package here needs Arduino.

substitutions:
  # Port pins (connector: 1 GND, 2 VP, 3 A, 4 B). A has 330R in series, B has 1k.
  p1_a: GPIO25
  p1_b: GPIO36  # input-only, no internal pull-up, never pulse_counter (errata)
  p2_a: GPIO26
  p2_b: GPIO39  # input-only, no internal pull-up, never pulse_counter (errata)
  p3_a: GPIO27
  p3_b: GPIO34  # input-only, ADC1
  p4_a: GPIO13
  p4_b: GPIO35  # input-only, ADC1
  p5_a: GPIO4
  p5_b: GPIO32  # bidirectional, ADC1
  p6_a: GPIO18
  p6_b: GPIO33  # bidirectional, ADC1
  uart_tx: GPIO17
  uart_rx: GPIO16  # through 10k/22k divider, 5 V safe
  i2c_sda: GPIO21  # 4.7k pull-ups fitted
  i2c_scl: GPIO22
  out_pin: GPIO23  # AO3400A low-side switch, off at boot
  # Spare header J902 (not fitted). GPIO5/GPIO14 output PWM at boot: inputs only.
  spare_19: GPIO19
  spare_14: GPIO14
  spare_5: GPIO5

esphome:
  name: ${device_name}
  friendly_name: ${friendly_name}
  min_version: 2026.10.2

esp32:
  board: esp32dev
  flash_size: 4MB

logger:

api:
  encryption:
    key: !secret api_key

ota:
  - platform: esphome
    encryption:  # reuses the api key, no separate OTA password

wifi:
  ssid: !secret wifi_ssid
  password: !secret wifi_password
  ap:
    ssid: ${device_name}

captive_portal:

status_led:
  pin:
    number: GPIO2
    ignore_strapping_warning: true  # GPIO2 is the status LED, active high

binary_sensor:
  - platform: gpio
    id: boot_button
    name: BOOT button
    pin:
      number: GPIO0
      inverted: true  # active low, 10k external pull-up
      ignore_strapping_warning: true
    filters:
      - delayed_on_off: 50ms
    entity_category: diagnostic

button:
  - platform: restart
    id: restart_button
    name: Restart

sensor:
  - platform: wifi_signal
    id: wifi_rssi
    name: Wi-Fi signal
    update_interval: 60s
  - platform: uptime
    id: uptime_s
    name: Uptime
